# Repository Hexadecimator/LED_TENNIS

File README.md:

# LED_TENNIS
ATMEGA328P-PU LED Volleyball Game

8 LEDs hooked up to arduino uno R3 digital input 0-7

2 push buttons hooked up to arduino uno R3 digital input 10 and 11

1 push button hooked up to reset

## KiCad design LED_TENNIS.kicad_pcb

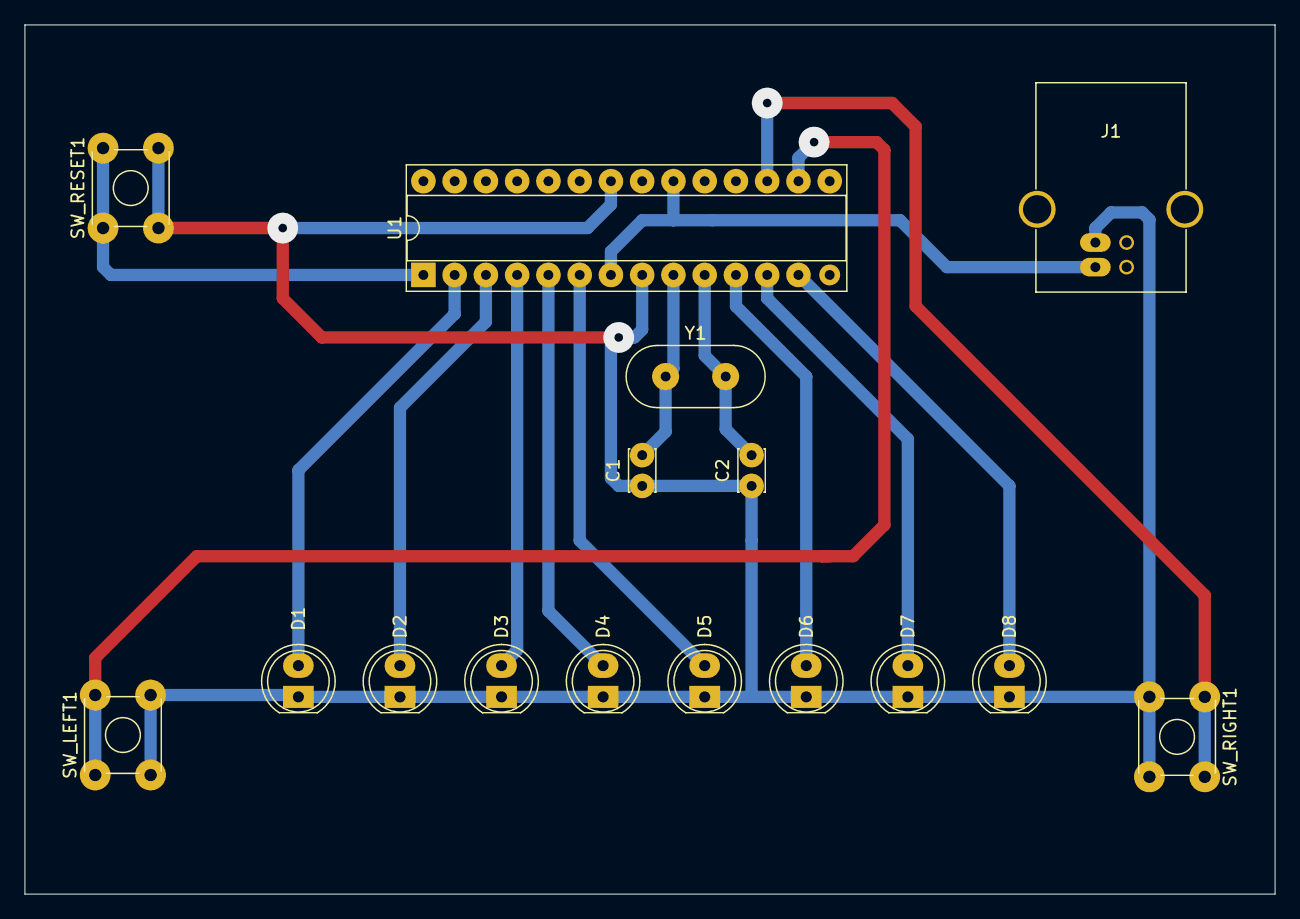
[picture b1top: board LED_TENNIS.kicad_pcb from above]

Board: 2 copper layers, 101.6 x 70.6 mm, 16 parts (0 on the bottom side), 15 nets.

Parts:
C1, C2: 22pF; C_Disc_D3.4mm_W2.1mm_P2.50mm
D1, D2, D3, D4, D5, D6, D7, D8: LED; LED_D5.0mm
J1: USB_B
SW_LEFT1: SW_MEC_5E; SW_TH_Tactile_Omron_B3F-10xx
SW_RESET1: SW_MEC_5E; SW_TH_Tactile_Omron_B3F-10xx
SW_RIGHT1: SW_MEC_5E; SW_TH_Tactile_Omron_B3F-10xx
U1: ATmega328P-PU; DIP-28_W7.62mm_Socket
Y1: Crystal; Crystal_HC49-U_Vertical

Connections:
/LED_0: D1.2, U1.2
/LED_1: D2.2, U1.3
/LED_2: D3.2, U1.4
/LED_3: D4.2, U1.5
/LED_4: D5.2, U1.6
/LED_5: D6.2, U1.11
/LED_6: D7.2, U1.12
/LED_7: D8.2, U1.13
/SW_LEFT: SW_LEFT1.1, SW_LEFT1.2, U1.16
/SW_RESET: SW_RESET1.1, SW_RESET1.2, U1.1
/SW_RIGHT: SW_RIGHT1.1, SW_RIGHT1.2, U1.17
GND: C1.1, C2.1, D1.1, D2.1, D3.1, D4.1, D5.1, D6.1, D7.1, D8.1, J1.4, SW_LEFT1.3, SW_LEFT1.4, SW_RESET1.3, SW_RESET1.4, SW_RIGHT1.3, SW_RIGHT1.4, U1.8, U1.22
VCC_5V: J1.1, U1.7, U1.20
XTAL1: C1.2, U1.9, Y1.1
XTAL2: C2.2, U1.10, Y1.2

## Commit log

2020-12-19 Add files via upload
    NOTE: F_Cu (front copper) is mirrored about the y-axis in order to be correctly oriented for the toner transfer process
2020-12-19 Add files via upload
    an attempt will be made to etch this QR code into copper
2020-12-19 Add files via upload
    edge cuts dimension: 4" horizontal, 3" vertical
2021-01-08 Update LED_TENNIS.ino
    Lesson learned: it is very difficult to employ the digital IO 0 and 1 pins because they are also the serial TX and RX pins for the ATMEGA328P-PU and their behavior is incredibly finnicky if you ultim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
2021-01-08 Add files via upload
    increased the size of the traces to facilitate easier toner transfer
2021-01-08 Update LED_TENNIS.ino
    fixed the order of myPins[] so that 8 and 9 are first (replacing digital IO pins 0 and 1)
